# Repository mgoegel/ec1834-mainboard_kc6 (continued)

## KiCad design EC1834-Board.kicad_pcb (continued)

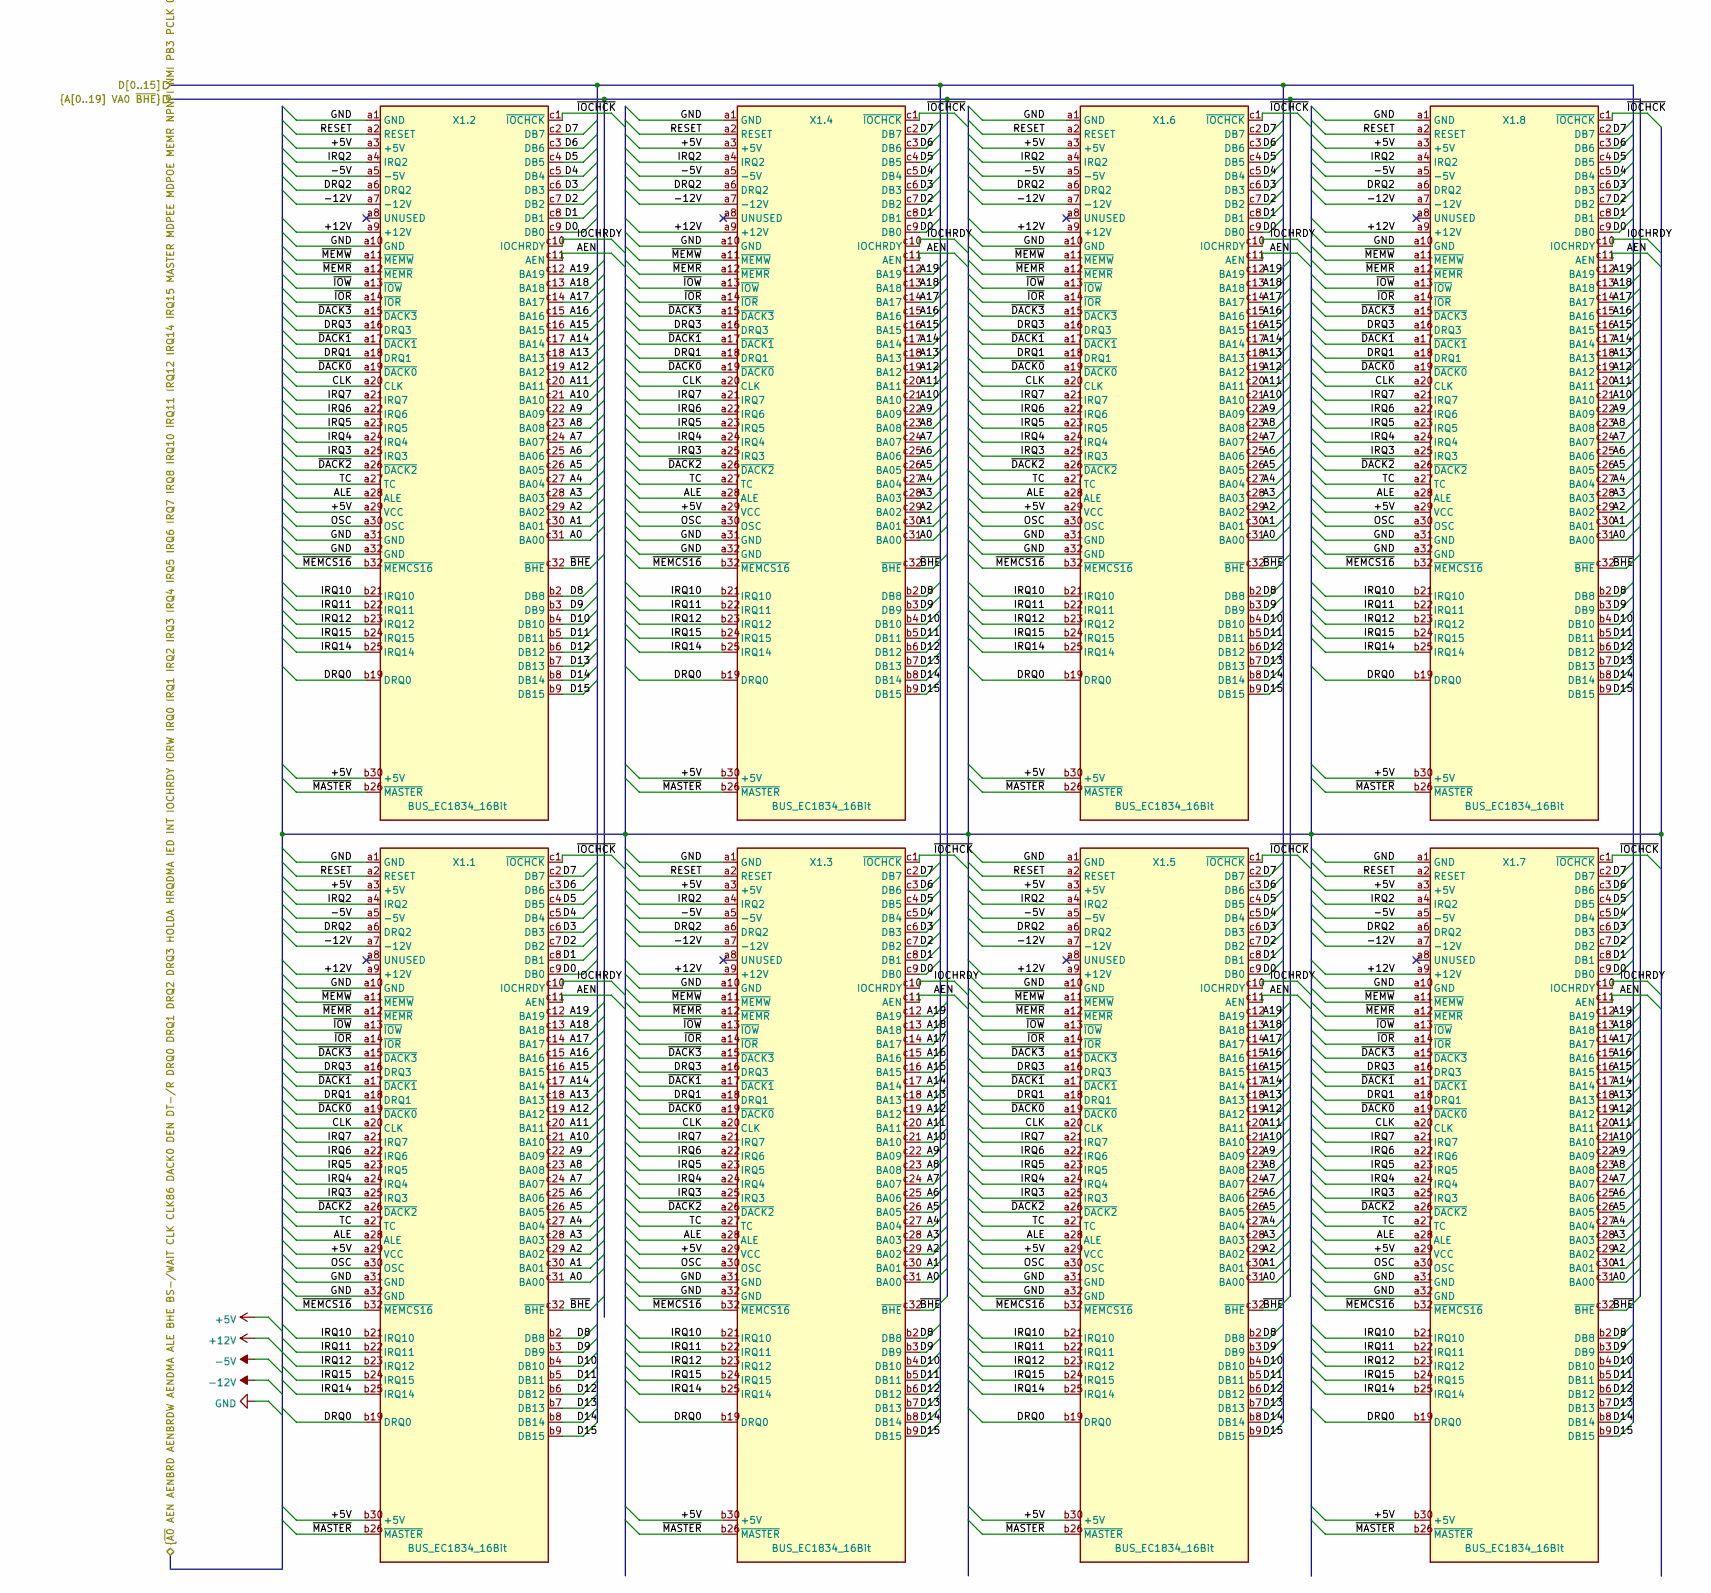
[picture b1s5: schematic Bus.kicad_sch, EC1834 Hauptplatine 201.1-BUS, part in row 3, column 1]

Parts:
X1.1, X1.2, X1.3, X1.4, X1.5, X1.6, X1.7, X1.8: BUS_EC1834_16Bit; DIN41612_C_3x32_Female_Vertical_THT

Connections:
+5V: X1.1.a3 (+5V), X1.1.a29 (VCC), X1.1.b30 (+5V), X1.2.a3 (+5V), X1.2.a29 (VCC), X1.2.b30 (+5V), X1.3.a3 (+5V), X1.3.a29 (VCC), X1.3.b30 (+5V), X1.4.a3 (+5V), X1.4.a29 (VCC), X1.4.b30 (+5V), X1.5.a3 (+5V), X1.5.a29 (VCC), X1.5.b30 (+5V), X1.6.a3 (+5V), X1.6.a29 (VCC), X1.6.b30 (+5V), X1.7.a3 (+5V), X1.7.a29 (VCC), X1.7.b30 (+5V), X1.8.a3 (+5V), X1.8.a29 (VCC), X1.8.b30 (+5V); also elsewhere on the board
+12V: X1.1.a9 (+12V), X1.2.a9 (+12V), X1.3.a9 (+12V), X1.4.a9 (+12V), X1.5.a9 (+12V), X1.6.a9 (+12V), X1.7.a9 (+12V), X1.8.a9 (+12V); also elsewhere on the board
-5V: X1.1.a5 (-5V), X1.2.a5 (-5V), X1.3.a5 (-5V), X1.4.a5 (-5V), X1.5.a5 (-5V), X1.6.a5 (-5V), X1.7.a5 (-5V), X1.8.a5 (-5V); also elsewhere on the board
-12V: X1.1.a7 (-12V), X1.2.a7 (-12V), X1.3.a7 (-12V), X1.4.a7 (-12V), X1.5.a7 (-12V), X1.6.a7 (-12V), X1.7.a7 (-12V), X1.8.a7 (-12V); also elsewhere on the board
/Bus/~IOCHCK: X1.1.c1 (~IOCHCK), X1.2.c1 (~IOCHCK), X1.3.c1 (~IOCHCK), X1.4.c1 (~IOCHCK), X1.5.c1 (~IOCHCK), X1.6.c1 (~IOCHCK), X1.7.c1 (~IOCHCK), X1.8.c1 (~IOCHCK)
/EC1834 201.1/A0: X1.1.c31 (BA00), X1.2.c31 (BA00), X1.3.c31 (BA00), X1.4.c31 (BA00), X1.5.c31 (BA00), X1.6.c31 (BA00), X1.7.c31 (BA00), X1.8.c31 (BA00); also elsewhere on the board
/EC1834 201.1/A1: X1.1.c30 (BA01), X1.2.c30 (BA01), X1.3.c30 (BA01), X1.4.c30 (BA01), X1.5.c30 (BA01), X1.6.c30 (BA01), X1.7.c30 (BA01), X1.8.c30 (BA01); also elsewhere on the board
/EC1834 201.1/A2: X1.1.c29 (BA02), X1.2.c29 (BA02), X1.3.c29 (BA02), X1.4.c29 (BA02), X1.5.c29 (BA02), X1.6.c29 (BA02), X1.7.c29 (BA02), X1.8.c29 (BA02); also elsewhere on the board
/EC1834 201.1/A3: X1.1.c28 (BA03), X1.2.c28 (BA03), X1.3.c28 (BA03), X1.4.c28 (BA03), X1.5.c28 (BA03), X1.6.c28 (BA03), X1.7.c28 (BA03), X1.8.c28 (BA03); also elsewhere on the board
/EC1834 201.1/A4: X1.1.c27 (BA04), X1.2.c27 (BA04), X1.3.c27 (BA04), X1.4.c27 (BA04), X1.5.c27 (BA04), X1.6.c27 (BA04), X1.7.c27 (BA04), X1.8.c27 (BA04); also elsewhere on the board
/EC1834 201.1/A5: X1.1.c26 (BA05), X1.2.c26 (BA05), X1.3.c26 (BA05), X1.4.c26 (BA05), X1.5.c26 (BA05), X1.6.c26 (BA05), X1.7.c26 (BA05), X1.8.c26 (BA05); also elsewhere on the board
/EC1834 201.1/A6: X1.1.c25 (BA06), X1.2.c25 (BA06), X1.3.c25 (BA06), X1.4.c25 (BA06), X1.5.c25 (BA06), X1.6.c25 (BA06), X1.7.c25 (BA06), X1.8.c25 (BA06); also elsewhere on the board
/EC1834 201.1/A7: X1.1.c24 (BA07), X1.2.c24 (BA07), X1.3.c24 (BA07), X1.4.c24 (BA07), X1.5.c24 (BA07), X1.6.c24 (BA07), X1.7.c24 (BA07), X1.8.c24 (BA07); also elsewhere on the board
/EC1834 201.1/A8: X1.1.c23 (BA08), X1.2.c23 (BA08), X1.3.c23 (BA08), X1.4.c23 (BA08), X1.5.c23 (BA08), X1.6.c23 (BA08), X1.7.c23 (BA08), X1.8.c23 (BA08); also elsewhere on the board
/EC1834 201.1/A9: X1.1.c22 (BA09), X1.2.c22 (BA09), X1.3.c22 (BA09), X1.4.c22 (BA09), X1.5.c22 (BA09), X1.6.c22 (BA09), X1.7.c22 (BA09), X1.8.c22 (BA09); also elsewhere on the board
/EC1834 201.1/A10: X1.1.c21 (BA10), X1.2.c21 (BA10), X1.3.c21 (BA10), X1.4.c21 (BA10), X1.5.c21 (BA10), X1.6.c21 (BA10), X1.7.c21 (BA10), X1.8.c21 (BA10); also elsewhere on the board
/EC1834 201.1/A11: X1.1.c20 (BA11), X1.2.c20 (BA11), X1.3.c20 (BA11), X1.4.c20 (BA11), X1.5.c20 (BA11), X1.6.c20 (BA11), X1.7.c20 (BA11), X1.8.c20 (BA11); also elsewhere on the board
/EC1834 201.1/A12: X1.1.c19 (BA12), X1.2.c19 (BA12), X1.3.c19 (BA12), X1.4.c19 (BA12), X1.5.c19 (BA12), X1.6.c19 (BA12), X1.7.c19 (BA12), X1.8.c19 (BA12); also elsewhere on the board
/EC1834 201.1/A13: X1.1.c18 (BA13), X1.2.c18 (BA13), X1.3.c18 (BA13), X1.4.c18 (BA13), X1.5.c18 (BA13), X1.6.c18 (BA13), X1.7.c18 (BA13), X1.8.c18 (BA13); also elsewhere on the board
/EC1834 201.1/A14: X1.1.c17 (BA14), X1.2.c17 (BA14), X1.3.c17 (BA14), X1.4.c17 (BA14), X1.5.c17 (BA14), X1.6.c17 (BA14), X1.7.c17 (BA14), X1.8.c17 (BA14); also elsewhere on the board
/EC1834 201.1/A15: X1.1.c16 (BA15), X1.2.c16 (BA15), X1.3.c16 (BA15), X1.4.c16 (BA15), X1.5.c16 (BA15), X1.6.c16 (BA15), X1.7.c16 (BA15), X1.8.c16 (BA15); also elsewhere on the board
/EC1834 201.1/A16: X1.1.c15 (BA16), X1.2.c15 (BA16), X1.3.c15 (BA16), X1.4.c15 (BA16), X1.5.c15 (BA16), X1.6.c15 (BA16), X1.7.c15 (BA16), X1.8.c15 (BA16); also elsewhere on the board
/EC1834 201.1/A17: X1.1.c14 (BA17), X1.2.c14 (BA17), X1.3.c14 (BA17), X1.4.c14 (BA17), X1.5.c14 (BA17), X1.6.c14 (BA17), X1.7.c14 (BA17), X1.8.c14 (BA17); also elsewhere on the board
/EC1834 201.1/A18: X1.1.c13 (BA18), X1.2.c13 (BA18), X1.3.c13 (BA18), X1.4.c13 (BA18), X1.5.c13 (BA18), X1.6.c13 (BA18), X1.7.c13 (BA18), X1.8.c13 (BA18); also elsewhere on the board
/EC1834 201.1/A19: X1.1.c12 (BA19), X1.2.c12 (BA19), X1.3.c12 (BA19), X1.4.c12 (BA19), X1.5.c12 (BA19), X1.6.c12 (BA19), X1.7.c12 (BA19), X1.8.c12 (BA19); also elsewhere on the board
/EC1834 201.1/AEN: X1.1.c11 (AEN), X1.2.c11 (AEN), X1.3.c11 (AEN), X1.4.c11 (AEN), X1.5.c11 (AEN), X1.6.c11 (AEN), X1.7.c11 (AEN), X1.8.c11 (AEN); also elsewhere on the board
/EC1834 201.1/ALE: X1.1.a28 (ALE), X1.2.a28 (ALE), X1.3.a28 (ALE), X1.4.a28 (ALE), X1.5.a28 (ALE), X1.6.a28 (ALE), X1.7.a28 (ALE), X1.8.a28 (ALE); also elsewhere on the board
/EC1834 201.1/CLK: X1.1.a20 (CLK), X1.2.a20 (CLK), X1.3.a20 (CLK), X1.4.a20 (CLK), X1.5.a20 (CLK), X1.6.a20 (CLK), X1.7.a20 (CLK), X1.8.a20 (CLK); also elsewhere on the board
/EC1834 201.1/D0: X1.1.c9 (DB0), X1.2.c9 (DB0), X1.3.c9 (DB0), X1.4.c9 (DB0), X1.5.c9 (DB0), X1.6.c9 (DB0), X1.7.c9 (DB0), X1.8.c9 (DB0); also elsewhere on the board
/EC1834 201.1/D1: X1.1.c8 (DB1), X1.2.c8 (DB1), X1.3.c8 (DB1), X1.4.c8 (DB1), X1.5.c8 (DB1), X1.6.c8 (DB1), X1.7.c8 (DB1), X1.8.c8 (DB1); also elsewhere on the board
/EC1834 201.1/D2: X1.1.c7 (DB2), X1.2.c7 (DB2), X1.3.c7 (DB2), X1.4.c7 (DB2), X1.5.c7 (DB2), X1.6.c7 (DB2), X1.7.c7 (DB2), X1.8.c7 (DB2); also elsewhere on the board
/EC1834 201.1/D3: X1.1.c6 (DB3), X1.2.c6 (DB3), X1.3.c6 (DB3), X1.4.c6 (DB3), X1.5.c6 (DB3), X1.6.c6 (DB3), X1.7.c6 (DB3), X1.8.c6 (DB3); also elsewhere on the board
/EC1834 201.1/D4: X1.1.c5 (DB4), X1.2.c5 (DB4), X1.3.c5 (DB4), X1.4.c5 (DB4), X1.5.c5 (DB4), X1.6.c5 (DB4), X1.7.c5 (DB4), X1.8.c5 (DB4); also elsewhere on the board
/EC1834 201.1/D5: X1.1.c4 (DB5), X1.2.c4 (DB5), X1.3.c4 (DB5), X1.4.c4 (DB5), X1.5.c4 (DB5), X1.6.c4 (DB5), X1.7.c4 (DB5), X1.8.c4 (DB5); also elsewhere on the board
/EC1834 201.1/D6: X1.1.c3 (DB6), X1.2.c3 (DB6), X1.3.c3 (DB6), X1.4.c3 (DB6), X1.5.c3 (DB6), X1.6.c3 (DB6), X1.7.c3 (DB6), X1.8.c3 (DB6); also elsewhere on the board
/EC1834 201.1/D7: X1.1.c2 (DB7), X1.2.c2 (DB7), X1.3.c2 (DB7), X1.4.c2 (DB7), X1.5.c2 (DB7), X1.6.c2 (DB7), X1.7.c2 (DB7), X1.8.c2 (DB7); also elsewhere on the board
/EC1834 201.1/D8: X1.1.b2 (DB8), X1.2.b2 (DB8), X1.3.b2 (DB8), X1.4.b2 (DB8), X1.5.b2 (DB8), X1.6.b2 (DB8), X1.7.b2 (DB8), X1.8.b2 (DB8); also elsewhere on the board
/EC1834 201.1/D9: X1.1.b3 (DB9), X1.2.b3 (DB9), X1.3.b3 (DB9), X1.4.b3 (DB9), X1.5.b3 (DB9), X1.6.b3 (DB9), X1.7.b3 (DB9), X1.8.b3 (DB9); also elsewhere on the board
/EC1834 201.1/D10: X1.1.b4 (DB10), X1.2.b4 (DB10), X1.3.b4 (DB10), X1.4.b4 (DB10), X1.5.b4 (DB10), X1.6.b4 (DB10), X1.7.b4 (DB10), X1.8.b4 (DB10); also elsewhere on the board
/EC1834 201.1/D11: X1.1.b5 (DB11), X1.2.b5 (DB11), X1.3.b5 (DB11), X1.4.b5 (DB11), X1.5.b5 (DB11), X1.6.b5 (DB11), X1.7.b5 (DB11), X1.8.b5 (DB11); also elsewhere on the board
/EC1834 201.1/D12: X1.1.b6 (DB12), X1.2.b6 (DB12), X1.3.b6 (DB12), X1.4.b6 (DB12), X1.5.b6 (DB12), X1.6.b6 (DB12), X1.7.b6 (DB12), X1.8.b6 (DB12); also elsewhere on the board
/EC1834 201.1/D13: X1.1.b7 (DB13), X1.2.b7 (DB13), X1.3.b7 (DB13), X1.4.b7 (DB13), X1.5.b7 (DB13), X1.6.b7 (DB13), X1.7.b7 (DB13), X1.8.b7 (DB13); also elsewhere on the board
/EC1834 201.1/D14: X1.1.b8 (DB14), X1.2.b8 (DB14), X1.3.b8 (DB14), X1.4.b8 (DB14), X1.5.b8 (DB14), X1.6.b8 (DB14), X1.7.b8 (DB14), X1.8.b8 (DB14); also elsewhere on the board
/EC1834 201.1/D15: X1.1.b9 (DB15), X1.2.b9 (DB15), X1.3.b9 (DB15), X1.4.b9 (DB15), X1.5.b9 (DB15), X1.6.b9 (DB15), X1.7.b9 (DB15), X1.8.b9 (DB15); also elsewhere on the board
/EC1834 201.1/DRQ0: X1.1.b19 (DRQ0), X1.2.b19 (DRQ0), X1.3.b19 (DRQ0), X1.4.b19 (DRQ0), X1.5.b19 (DRQ0), X1.6.b19 (DRQ0), X1.7.b19 (DRQ0), X1.8.b19 (DRQ0); also elsewhere on the board
/EC1834 201.1/DRQ1: X1.1.a18 (DRQ1), X1.2.a18 (DRQ1), X1.3.a18 (DRQ1), X1.4.a18 (DRQ1), X1.5.a18 (DRQ1), X1.6.a18 (DRQ1), X1.7.a18 (DRQ1), X1.8.a18 (DRQ1); also elsewhere on the board
/EC1834 201.1/DRQ2: X1.1.a6 (DRQ2), X1.2.a6 (DRQ2), X1.3.a6 (DRQ2), X1.4.a6 (DRQ2), X1.5.a6 (DRQ2), X1.6.a6 (DRQ2), X1.7.a6 (DRQ2), X1.8.a6 (DRQ2); also elsewhere on the board
/EC1834 201.1/DRQ3: X1.1.a16 (DRQ3), X1.2.a16 (DRQ3), X1.3.a16 (DRQ3), X1.4.a16 (DRQ3), X1.5.a16 (DRQ3), X1.6.a16 (DRQ3), X1.7.a16 (DRQ3), X1.8.a16 (DRQ3); also elsewhere on the board
/EC1834 201.1/IOCHRDY: X1.1.c10 (IOCHRDY), X1.2.c10 (IOCHRDY), X1.3.c10 (IOCHRDY), X1.4.c10 (IOCHRDY), X1.5.c10 (IOCHRDY), X1.6.c10 (IOCHRDY), X1.7.c10 (IOCHRDY), X1.8.c10 (IOCHRDY); also elsewhere on the board
/EC1834 201.1/IRQ2: X1.1.a4 (IRQ2), X1.2.a4 (IRQ2), X1.3.a4 (IRQ2), X1.4.a4 (IRQ2), X1.5.a4 (IRQ2), X1.6.a4 (IRQ2), X1.7.a4 (IRQ2), X1.8.a4 (IRQ2); also elsewhere on the board
/EC1834 201.1/IRQ3: X1.1.a25 (IRQ3), X1.2.a25 (IRQ3), X1.3.a25 (IRQ3), X1.4.a25 (IRQ3), X1.5.a25 (IRQ3), X1.6.a25 (IRQ3), X1.7.a25 (IRQ3), X1.8.a25 (IRQ3); also elsewhere on the board
/EC1834 201.1/IRQ4: X1.1.a24 (IRQ4), X1.2.a24 (IRQ4), X1.3.a24 (IRQ4), X1.4.a24 (IRQ4), X1.5.a24 (IRQ4), X1.6.a24 (IRQ4), X1.7.a24 (IRQ4), X1.8.a24 (IRQ4); also elsewhere on the board
/EC1834 201.1/IRQ5: X1.1.a23 (IRQ5), X1.2.a23 (IRQ5), X1.3.a23 (IRQ5), X1.4.a23 (IRQ5), X1.5.a23 (IRQ5), X1.6.a23 (IRQ5), X1.7.a23 (IRQ5), X1.8.a23 (IRQ5); also elsewhere on the board
/EC1834 201.1/IRQ6: X1.1.a22 (IRQ6), X1.2.a22 (IRQ6), X1.3.a22 (IRQ6), X1.4.a22 (IRQ6), X1.5.a22 (IRQ6), X1.6.a22 (IRQ6), X1.7.a22 (IRQ6), X1.8.a22 (IRQ6); also elsewhere on the board
/EC1834 201.1/IRQ7: X1.1.a21 (IRQ7), X1.2.a21 (IRQ7), X1.3.a21 (IRQ7), X1.4.a21 (IRQ7), X1.5.a21 (IRQ7), X1.6.a21 (IRQ7), X1.7.a21 (IRQ7), X1.8.a21 (IRQ7); also elsewhere on the board
/EC1834 201.1/IRQ10: X1.1.b21 (IRQ10), X1.2.b21 (IRQ10), X1.3.b21 (IRQ10), X1.4.b21 (IRQ10), X1.5.b21 (IRQ10), X1.6.b21 (IRQ10), X1.7.b21 (IRQ10), X1.8.b21 (IRQ10); also elsewhere on the board
/EC1834 201.1/IRQ11: X1.1.b22 (IRQ11), X1.2.b22 (IRQ11), X1.3.b22 (IRQ11), X1.4.b22 (IRQ11), X1.5.b22 (IRQ11), X1.6.b22 (IRQ11), X1.7.b22 (IRQ11), X1.8.b22 (IRQ11); also elsewhere on the board
/EC1834 201.1/IRQ12: X1.1.b23 (IRQ12), X1.2.b23 (IRQ12), X1.3.b23 (IRQ12), X1.4.b23 (IRQ12), X1.5.b23 (IRQ12), X1.6.b23 (IRQ12), X1.7.b23 (IRQ12), X1.8.b23 (IRQ12); also elsewhere on the board
/EC1834 201.1/IRQ14: X1.1.b25 (IRQ14), X1.2.b25 (IRQ14), X1.3.b25 (IRQ14), X1.4.b25 (IRQ14), X1.5.b25 (IRQ14), X1.6.b25 (IRQ14), X1.7.b25 (IRQ14), X1.8.b25 (IRQ14); also elsewhere on the board
/EC1834 201.1/IRQ15: X1.1.b24 (IRQ15), X1.2.b24 (IRQ15), X1.3.b24 (IRQ15), X1.4.b24 (IRQ15), X1.5.b24 (IRQ15), X1.6.b24 (IRQ15), X1.7.b24 (IRQ15), X1.8.b24 (IRQ15); also elsewhere on the board
/EC1834 201.1/OSC: X1.1.a30 (OSC), X1.2.a30 (OSC), X1.3.a30 (OSC), X1.4.a30 (OSC), X1.5.a30 (OSC), X1.6.a30 (OSC), X1.7.a30 (OSC), X1.8.a30 (OSC); also elsewhere on the board
/EC1834 201.1/RESET: X1.1.a2 (RESET), X1.2.a2 (RESET), X1.3.a2 (RESET), X1.4.a2 (RESET), X1.5.a2 (RESET), X1.6.a2 (RESET), X1.7.a2 (RESET), X1.8.a2 (RESET); also elsewhere on the board
/EC1834 201.1/TC: X1.1.a27 (TC), X1.2.a27 (TC), X1.3.a27 (TC), X1.4.a27 (TC), X1.5.a27 (TC), X1.6.a27 (TC), X1.7.a27 (TC), X1.8.a27 (TC); also elsewhere on the board
/EC1834 201.1/~BHE: X1.1.c32 (~BHE), X1.2.c32 (~BHE), X1.3.c32 (~BHE), X1.4.c32 (~BHE), X1.5.c32 (~BHE), X1.6.c32 (~BHE), X1.7.c32 (~BHE), X1.8.c32 (~BHE); also elsewhere on the board
/EC1834 201.1/~DACK0: X1.1.a19 (~DACK0), X1.2.a19 (~DACK0), X1.3.a19 (~DACK0), X1.4.a19 (~DACK0), X1.5.a19 (~DACK0), X1.6.a19 (~DACK0), X1.7.a19 (~DACK0), X1.8.a19 (~DACK0); also elsewhere on the board
/EC1834 201.1/~DACK1: X1.1.a17 (~DACK1), X1.2.a17 (~DACK1), X1.3.a17 (~DACK1), X1.4.a17 (~DACK1), X1.5.a17 (~DACK1), X1.6.a17 (~DACK1), X1.7.a17 (~DACK1), X1.8.a17 (~DACK1); also elsewhere on the board
/EC1834 201.1/~DACK2: X1.1.a26 (~DACK2), X1.2.a26 (~DACK2), X1.3.a26 (~DACK2), X1.4.a26 (~DACK2), X1.5.a26 (~DACK2), X1.6.a26 (~DACK2), X1.7.a26 (~DACK2), X1.8.a26 (~DACK2); also elsewhere on the board
/EC1834 201.1/~DACK3: X1.1.a15 (~DACK3), X1.2.a15 (~DACK3), X1.3.a15 (~DACK3), X1.4.a15 (~DACK3), X1.5.a15 (~DACK3), X1.6.a15 (~DACK3), X1.7.a15 (~DACK3), X1.8.a15 (~DACK3); also elsewhere on the board
/EC1834 201.1/~IOR: X1.1.a14 (~IOR), X1.2.a14 (~IOR), X1.3.a14 (~IOR), X1.4.a14 (~IOR), X1.5.a14 (~IOR), X1.6.a14 (~IOR), X1.7.a14 (~IOR), X1.8.a14 (~IOR); also elsewhere on the board
/EC1834 201.1/~IOW: X1.1.a13 (~IOW), X1.2.a13 (~IOW), X1.3.a13 (~IOW), X1.4.a13 (~IOW), X1.5.a13 (~IOW), X1.6.a13 (~IOW), X1.7.a13 (~IOW), X1.8.a13 (~IOW); also elsewhere on the board
/EC1834 201.1/~MASTER: X1.1.b26 (~MASTER), X1.2.b26 (~MASTER), X1.3.b26 (~MASTER), X1.4.b26 (~MASTER), X1.5.b26 (~MASTER), X1.6.b26 (~MASTER), X1.7.b26 (~MASTER), X1.8.b26 (~MASTER); also elsewhere on the board
/EC1834 201.1/~MEMCS16: X1.1.b32 (~MEMCS16), X1.2.b32 (~MEMCS16), X1.3.b32 (~MEMCS16), X1.4.b32 (~MEMCS16), X1.5.b32 (~MEMCS16), X1.6.b32 (~MEMCS16), X1.7.b32 (~MEMCS16), X1.8.b32 (~MEMCS16); also elsewhere on the board
/EC1834 201.1/~MEMR: X1.1.a12 (~MEMR), X1.2.a12 (~MEMR), X1.3.a12 (~MEMR), X1.4.a12 (~MEMR), X1.5.a12 (~MEMR), X1.6.a12 (~MEMR), X1.7.a12 (~MEMR), X1.8.a12 (~MEMR); also elsewhere on the board
/EC1834 201.1/~MEMW: X1.1.a11 (~MEMW), X1.2.a11 (~MEMW), X1.3.a11 (~MEMW), X1.4.a11 (~MEMW), X1.5.a11 (~MEMW), X1.6.a11 (~MEMW), X1.7.a11 (~MEMW), X1.8.a11 (~MEMW); also elsewhere on the board
GND: X1.1.a1 (GND), X1.1.a10 (GND), X1.1.a31 (GND), X1.1.a32 (GND), X1.2.a1 (GND), X1.2.a10 (GND), X1.2.a31 (GND), X1.2.a32 (GND), X1.3.a1 (GND), X1.3.a10 (GND), X1.3.a31 (GND), X1.3.a32 (GND), X1.4.a1 (GND), X1.4.a10 (GND), X1.4.a31 (GND), X1.4.a32 (GND), X1.5.a1 (GND), X1.5.a10 (GND), X1.5.a31 (GND), X1.5.a32 (GND), X1.6.a1 (GND), X1.6.a10 (GND), X1.6.a31 (GND), X1.6.a32 (GND), X1.7.a1 (GND), X1.7.a10 (GND), X1.7.a31 (GND), X1.7.a32 (GND), X1.8.a1 (GND), X1.8.a10 (GND), X1.8.a31 (GND), X1.8.a32 (GND); also elsewhere on the board

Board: 6 copper layers, 345 parts (0 on the bottom side), 432 nets, no tracks yet.

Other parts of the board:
RES2, RES3, RES4: DIP-16_W7.62mm
RES6: DIP-20_W7.62mm

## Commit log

2022-09-17 Added more ICs Added README
2022-09-17 Update Readme.MD
    line breaks in README
2022-09-17 Update Readme.MD
    linebreak fixed
2022-12-03 Switch to Kicad 6
2022-12-17 Improved schematics and docs
2022-12-18 Improved schematics
2022-12-20 Almsot completed page 1
2022-12-20 prevent checkin of backups
2022-12-20 removed backup files
2022-12-22 Completed signal connections Work on bus signal names
2022-12-23 Completed main bus signal label on CPU page
2022-12-24 Corrected schema names added bus signals
2022-12-25 corrected page names progress on page 2 added 1834 bus symbol
2022-12-28 Schematics almost done, need to connect busses
2022-12-28 Page 1 & 2 connected Hierarchival connections created and tested
2022-12-29 Completed BUS Final checks required
2022-12-29 Replaced PDF
2022-12-30 Small corrections on Page 201.1
2023-01-01 Updated footprint for EMR UC8821 Added footprint for PS5 PCB layout in progress small corrections in schematics
2023-01-02 Updated footprints Updated PCB
2023-01-03 Completed PCB layout Changed PS5
2023-01-05 Small optical changes
2023-01-14 Updated some symbol pins no more error on PCB import due to leading zero on pin number also fixed missing network connections added unused pin connections on bus connectors
2023-01-14 Wrong Signal fixed
2023-01-22 Small improvements
2023-01-23 Replaced/corrected D70 from DL008 with DL000 Updated schematics
2023-01-23 Updated git ignore
2023-01-23 removed backup file
2023-01-24 Fixed wrong symbol (some DL008 are 74S00)
2023-02-05 Modifications to pass most ERC checks modified symbols for ERC check Added some notes
2023-02-15 Updated ec1834 symbols Fixed missing D8-D15 on bus connector Updated PDFs
2023-02-19 Added some notes to schematics
2023-03-06 Changed WD1-5 connections - open > bridged
2023-06-06 Some corrections in schematics
